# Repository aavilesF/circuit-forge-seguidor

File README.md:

# circuit-forge-seguidor

> **Rama `seguidor-caseroV2`: lo vigente está en `v2/` (ver `v2/README.md` y `CLAUDE.md`). El resto es histórico salvo excepciones documentadas en `v2/docs/ESTADO-DOCUMENTOS.md`.**

Robot seguidor de línea para **Robolympics RMX2026** (Tecnológico de Monterrey, Campus León).
Equipo **Circuit Forge**: diseño, firmware, pruebas y registro de resultados.

## Objetivo

Construir un robot autónomo, ligero y estable que recorra el circuito en el menor tiempo posible sin salirse de la línea. Prioridad del equipo: ganar; mínimo aceptable, completar la pista sin salirse. Se busca un buen equilibrio entre precisión de los sensores y velocidad.

## Competencia

| Dato | Valor |
|---|---|
| Evento | Robolympics RMX2026, categoría Seguidores de línea |
| Fecha | Sábado 21 de noviembre de 2026, 8:00 a 16:00 h |
| Sede | Tec de Monterrey, Campus León |
| Registro | Hasta el 17 de noviembre de 2026, 6:00 pm (confirmación por correo el 18 de noviembre) |
| Donación | Alimentos por $300 MXN por robot, se entregan el 21 de noviembre al registrarse |
| Reglamento | Ver [docs/requisitos.md](docs/requisitos.md) |

Las reglas pueden modificarse a más tardar el 18 de noviembre y se comunican por correo a los equipos registrados.

## Equipo

| Integrante | Rol |
|---|---|
| Alejandro Avilés Flores | Por definir |
| Alan Uzuel Vargas Zavala | Por definir |
| Daniel Navarro Robledo | Por definir |

## Estado actual

- Repositorio creado y reglamento analizado (ver `docs/requisitos.md`).
- Microcontrolador: **ESP32** (decidido, D3). El resto de la arquitectura sigue como propuesta sin aprobar (`docs/plan.md`).
- Componentes: **sin comprar** (compra prevista la semana del 2 de noviembre). El sensor (QTR-8A o curvo de 24) sigue sin decidir.
- Firmware: **lógica probada en computadora** (60 pruebas) y **simulador** de la pista. Capa de hardware del ESP32 escrita pero **solo verificada de sintaxis**: no se ha compilado con el SDK real ni probado en la placa.
- Diagramas y guía de armado listos; las medidas de las piezas son nominales hasta tenerlas en la mano.
- Pista de práctica: **por construir**.

## Contenido

| Archivo | Para qué sirve |
|---|---|
| [docs/requisitos.md](docs/requisitos.md) | Restricciones del reglamento y de la convocatoria |
| [docs/presupuesto.md](docs/presupuesto.md) | Lista de compra y presupuesto |
| [docs/decisiones.md](docs/decisiones.md) | Registro de decisiones del equipo |
| [docs/plan.md](docs/plan.md) | Plan de 4 semanas y arquitectura propuesta (aún sin aprobar) |
| [docs/contexto-ia.md](docs/contexto-ia.md) | Resumen del proyecto y prompt de arranque para que cualquier IA o persona parta del mismo contexto |
| [modificaciones/](modificaciones/README.md) | Propuestas de cambio de cada integrante, sin tocar los documentos originales |

| [docs/simulacion.md](docs/simulacion.md) | Modelo virtual, matemáticas explicadas, resultados y límites del simulador |
| [docs/electronica.md](docs/electronica.md) | Reglas eléctricas, pines (`docs/diagramas/pines.md`), batería y sensores |
| [docs/mecanica.md](docs/mecanica.md) | Geometría, velocidades, distribución de peso |
| [docs/armado.md](docs/armado.md) | Guía de armado y pruebas por etapas, con criterios de aprobado |
| `docs/diagramas/` | Diagrama de bloques, cableado, vistas superiores a escala y gráficas de simulación |
| `firmware/seguidor/` | Firmware (ESP32, Arduino IDE o PlatformIO): `pines.h` es la única fuente de los pines |
| `pruebas/` | `ejecutar.sh` (lógica, g++) y `verificar_sintaxis_esp32.sh` (hardware contra un stub) |
| `simulacion/` | Simulador en lazo cerrado que usa el mismo código de control; resultados en `resultados/` |
| `herramientas/generar_diagramas.py` | Regenera diagramas, tabla de pines y gráficas |

### Comandos rápidos

```bash
pruebas/ejecutar.sh                    # pruebas de la lógica
simulacion/ejecutar.sh                 # simulación con los parámetros por defecto
pruebas/verificar_sintaxis_esp32.sh    # sintaxis del código de hardware (no es compilación real)
python3 herramientas/generar_diagramas.py
```

## Forma de trabajo

- Cambios pequeños con commits descriptivos.
- Los cambios propuestos por los integrantes van en `modificaciones/` (ver su README), no directamente en `README.md` ni en `docs/`.
- Toda decisión de hardware o de interfaces se anota en `docs/decisiones.md`.
- Nada se da por terminado sin evidencia (foto, medición o registro de prueba).

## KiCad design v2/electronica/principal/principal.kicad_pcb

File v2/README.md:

# Seguidor de Línea V2 — rama `seguidor-caseroV2`

Creada el 12 nov 2026 desde `engineering/robot-casero` (commit f9a4700). **Todo lo vigente está en `v2/`.**
El resto de carpetas del repositorio (docs/, electronica/kicad/, mecanica/, firmware/, robot-casero/) se heredó de la rama
anterior y es **HISTÓRICO**: sirve de consulta, no es diseño vigente. No se borró nada.

| Carpeta | Contenido | Estado |
|---|---|---|
| `v2/docs/decisiones.md` | Decisiones vigentes (D-V2-xx) con su origen | vigente |
| `v2/inventario.csv` | **Fuente maestra del inventario** (comprado / usado / recepción) | vigente |
| `v2/docs/componentes.md` | Tabla **generada** desde el inventario; no se edita a mano | vigente |
| `v2/docs/ESTADO-DOCUMENTOS.md` | Qué documentos son vigentes y cuáles históricos | vigente |
| `v2/herramientas/validar_repo.py` | Validador de coherencia (inventario vs esquemas, términos obsoletos, IDs, DRC) | vigente |
| `docs/pendientes-por-confirmar.md` | **Lista única de pendientes** (v10, incluye P-V2-xx) | vigente |
| `v2/docs/conexiones.md` | Qué se conecta con qué y por qué; análisis 3.3 V vs 5 V | vigente |
| `v2/docs/bibliotecas.md` | Qué símbolo usa cada pieza y de dónde viene | vigente |
| `v2/docs/migracion.md` | Qué se migró, qué se corrigió y qué queda histórico | vigente |
| `v2/electronica/principal/` y `sensores/` | Esquemáticos KiCad 10 (copia de los de `SDL V2 General/KiCAD/Esquemas V2`) | esquemas aprobados (D-V2-20) |
| `v2/electronica/principal/` y `sensores/` `.kicad_pcb` | PCB ruteadas, DRC 0 errores (15 nov); sensores = opción B (D-V2-25); la A en `sensores/alternativa_68mm_curva/` | en revisión de Alan |
| `v2/electronica/prototipo-emergencia/` | Prototipo de emergencia en placa perforada: esquema unificado y `GUIA-FIRMWARE.md` | vigente, alternativa (D-V2-40) |
| `v2/firmware/emergencia/` | **Firmware vigente** del prototipo de emergencia, versión 2.0 (carga, consola, ajustes sin recompilar, primera conexión) | compilado y probado en PC; falta prueba física (EM-08) |
| `v2/electronica/vistas/` | SVG/PNG de esquemas y vistas 3D de la colocación | — |
| `v2/docs/evaluaciones.md` | Encoders/aprendizaje y ventilador (EN ESTUDIO) | — |
| `v2/electronica/herramientas/` | Scripts que generan esquemas, colocación y ruteo | — |

Etapas: 1 esquemáticos (aprobados) → 2 PCB de doble cara (ruteadas, en revisión; sin archivos de fabricación) → 3 compatibilidad mecánica.
Reglas de trabajo: `CLAUDE.md` en la raíz.

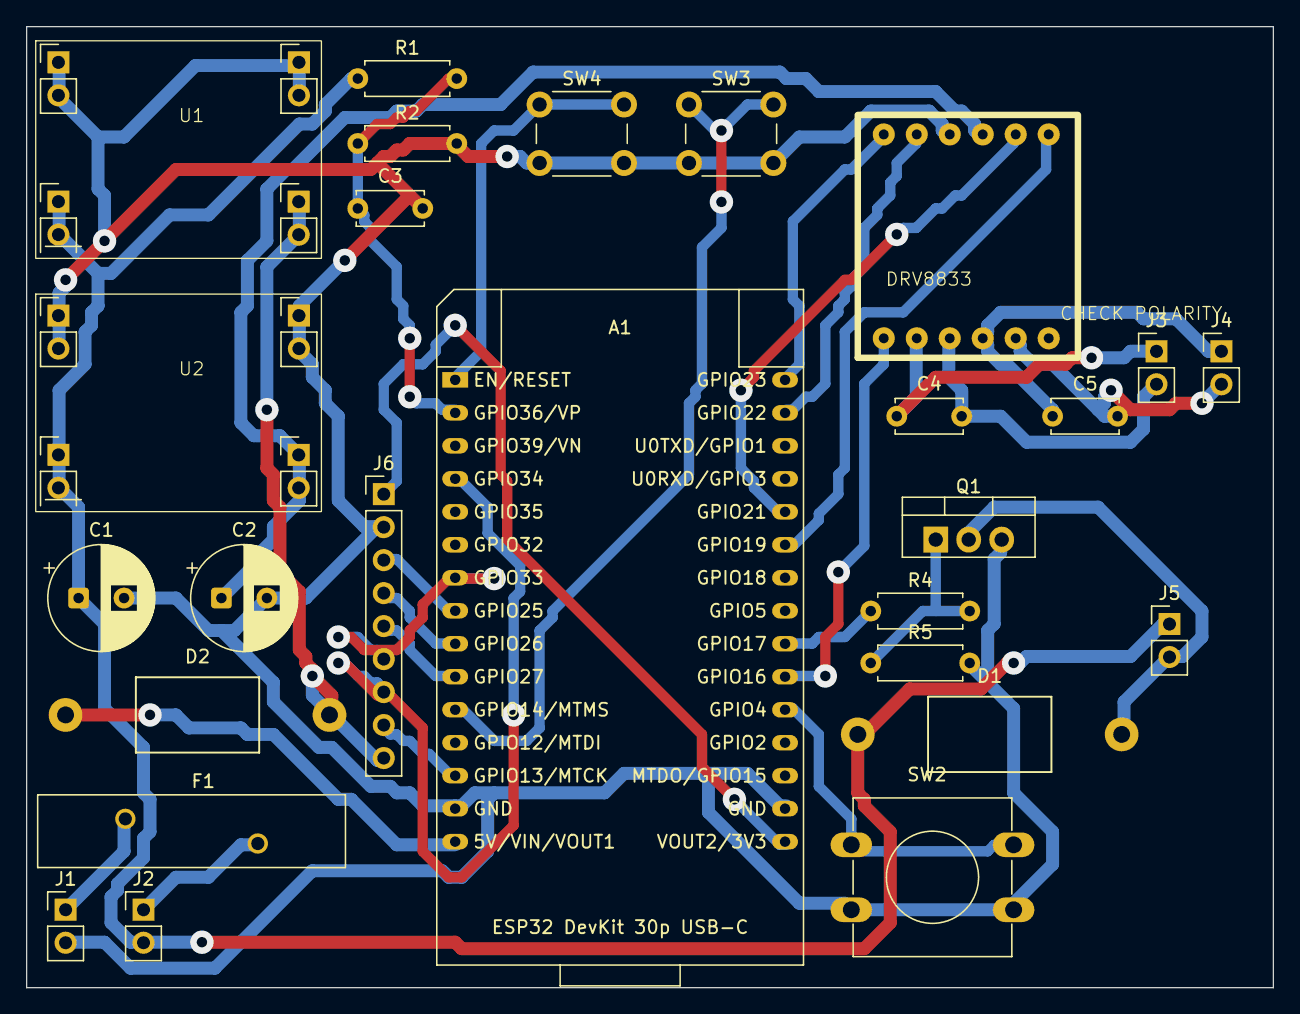
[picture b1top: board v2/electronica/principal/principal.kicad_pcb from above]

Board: 2 copper layers, 96.0 x 74.0 mm, 26 parts (0 on the bottom side), 30 nets.

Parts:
A1: ESP32 DevKit 30p USB-C; ESP32-DevKit-USB-C
C1, C2: 470uF 16V; CP_Radial_D8.0mm_P3.50mm
C3, C4, C5: 100nF; C_Disc_D5.0mm_W2.5mm_P5.00mm
D1, D2: 1N5822; D_DO-201AD_P20.32mm_Taladro1.3
F1: PTC 1.5A >=16V (por comprar); Fuse_BelFuse_0ZRE0150FF_L23.4mm_W5.3mm
J1: Bateria JST-RC; PinHeader_1x02_P2.54mm_Vertical
J2: Interruptor KCD1; PinHeader_1x02_P2.54mm_Vertical
J3: Motor izq.; PinHeader_1x02_P2.54mm_Vertical
J4: Motor der.; PinHeader_1x02_P2.54mm_Vertical
J5: Ventilador; PinHeader_1x02_P2.54mm_Vertical
J6: A sensores; PinHeader_1x09_P2.54mm_Vertical
Q1: IRLZ44N; TO-220-3_Vertical
R1: 100k; R_Axial_DIN0207_L6.3mm_D2.5mm_P7.62mm_Horizontal
R2: 33k; R_Axial_DIN0207_L6.3mm_D2.5mm_P7.62mm_Horizontal
R4: 100; R_Axial_DIN0207_L6.3mm_D2.5mm_P7.62mm_Horizontal
R5: 10k; R_Axial_DIN0207_L6.3mm_D2.5mm_P7.62mm_Horizontal
SW2: START 12x12; SW_PUSH-12mm
SW3: CAL 6x6; SW_PUSH_6mm
SW4: RESET 6x6; SW_PUSH_6mm
U1: MP1584 -> 5.0 V; MP1584module
U2: MP1584 -> 6.0 V (motores); MP1584module
U3: Modulo DRV8833; DRV8833

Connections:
+3V3: A1.16, J6.1
/+5V: D2.2, J6.9, U1.4
/+6V_MOT: C2.1, U2.4, U3.10
/AIN1: A1.25, U3.7
/AIN2: A1.26, U3.8
/BIN1: A1.29, U3.11
/BIN2: A1.30, U3.12
/CAL: A1.11, SW3.1
/DRV_SLEEP: A1.21, U3.1
/EMIT_EN: A1.13, J6.8
/EN: A1.1, SW4.1
/ESP_5V: A1.15, D2.1
/FAN_G: Q1.1, R4.2, R5.1
/FAN_PWM: A1.22, R4.1
/FAN_SW: D1.2, J5.2, Q1.2
/MOTL_A: C4.1, J3.1, U3.2
/MOTL_B: C4.2, J3.2, U3.3
/MOTR_A: C5.1, J4.1, U3.4
/MOTR_B: C5.2, J4.2, U3.5
/S0: A1.8, J6.3
/S1: A1.9, J6.4
/S2: A1.10, J6.5
/S3: A1.7, J6.6
/SIG: A1.4, J6.7
/START: A1.20, SW2.1
/VBAT_F: F1.2, J2.1
/VBAT_RAW: F1.1, J1.1
/VBAT_SENSE: A1.2, C3.1, R1.2, R2.1
/VBAT_SW: C1.1, D1.1, J2.2, J5.1, R1.1, U1.1, U2.1
GND: A1.14, A1.17, C1.2, C2.2, C3.2, J1.2, J6.2, Q1.3, R2.2, R5.2, SW2.2, SW3.2, SW4.2, U1.2, U1.3, U2.2, U2.3, U3.9

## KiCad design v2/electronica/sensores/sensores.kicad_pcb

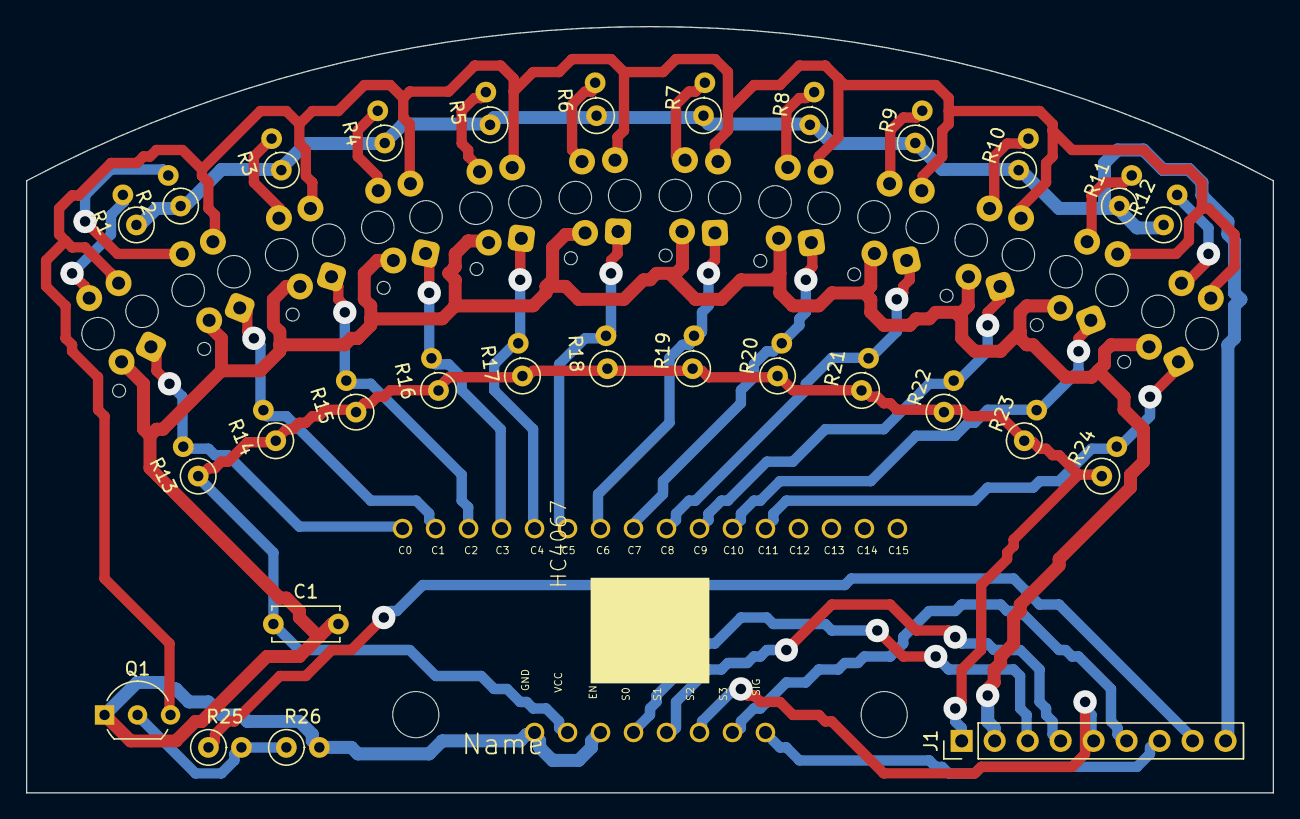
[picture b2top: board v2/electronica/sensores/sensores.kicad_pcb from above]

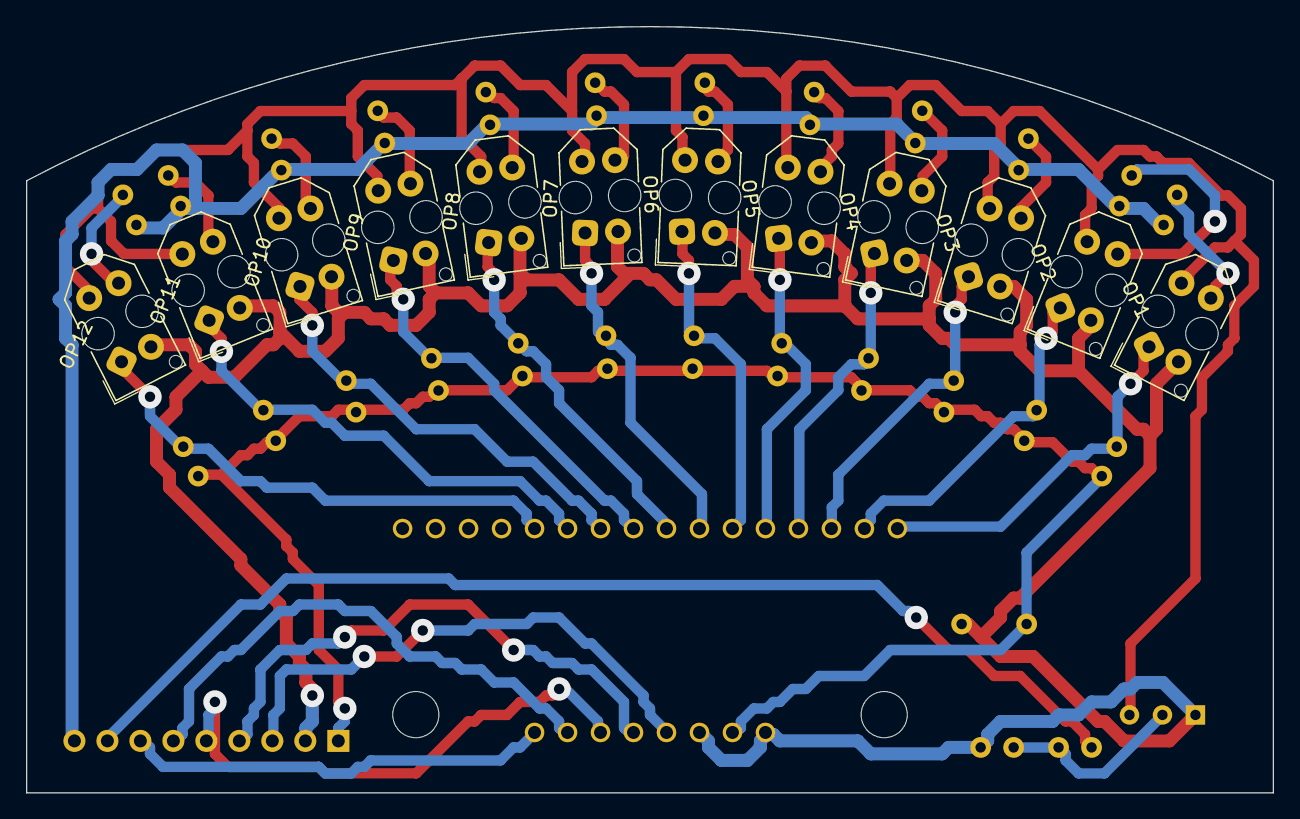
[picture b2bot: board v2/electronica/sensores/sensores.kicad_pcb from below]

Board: 2 copper layers, 96.0 x 59.0 mm, 42 parts (12 on the bottom side), 35 nets.

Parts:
C1: 100nF; C_Disc_D5.0mm_W2.5mm_P5.00mm
J1: A principal; PinHeader_1x09_P2.54mm_Vertical
OP1, OP2, OP3, OP4, OP5, OP6, OP7, OP8, OP9, OP10, OP11, OP12: TCRT5000; Vishay_TCRT5000
Q1: 2N2222 E-B-C; TO-92_Inline_Wide
R1, R2, R3, R4, R5, R6, R7, R8, R9, R10, R11, R12: 220; R_Axial_DIN0207_L6.3mm_D2.5mm_P2.54mm_Vertical
R13, R14, R15, R16, R17, R18, R19, R20, R21, R22, R23, R24, R26: 10k; R_Axial_DIN0207_L6.3mm_D2.5mm_P2.54mm_Vertical
R25: 470; R_Axial_DIN0207_L6.3mm_D2.5mm_P2.54mm_Vertical
U1: Modulo CD74HC4067; ANALOG_MUX_BREAKOUT_HC4067

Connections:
+3V3: C1.1, J1.1, R13.1, R14.1, R15.1, R16.1, R17.1, R18.1, R19.1, R20.1, R21.1, R22.1, R23.1, R24.1, U1.VCC
+5V: J1.9, R1.1, R2.1, R3.1, R4.1, R5.1, R6.1, R7.1, R8.1, R9.1, R10.1, R11.1, R12.1
/BASE_Q1: Q1.2, R25.2, R26.1
/EMIT_EN: J1.8, R25.1
/EMIT_K: OP1.4, OP2.4, OP3.4, OP4.4, OP5.4, OP6.4, OP7.4, OP8.4, OP9.4, OP10.4, OP11.4, OP12.4, Q1.3
/LEDA1: OP1.3, R1.2
/LEDA2: OP2.3, R2.2
/LEDA3: OP3.3, R3.2
/LEDA4: OP4.3, R4.2
/LEDA5: OP5.3, R5.2
/LEDA6: OP6.3, R6.2
/LEDA7: OP7.3, R7.2
/LEDA8: OP8.3, R8.2
/LEDA9: OP9.3, R9.2
/LEDA10: OP10.3, R10.2
/LEDA11: OP11.3, R11.2
/LEDA12: OP12.3, R12.2
/S0: J1.3, U1.S0
/S1: J1.4, U1.S1
/S2: J1.5, U1.S2
/S3: J1.6, U1.S3
/SEN1: OP1.1, R13.2, U1.C0
/SEN2: OP2.1, R14.2, U1.C1
/SEN3: OP3.1, R15.2, U1.C2
/SEN4: OP4.1, R16.2, U1.C3
/SEN5: OP5.1, R17.2, U1.C4
/SEN6: OP6.1, R18.2, U1.C5
/SEN7: OP7.1, R19.2, U1.C6
/SEN8: OP8.1, R20.2, U1.C7
/SEN9: OP9.1, R21.2, U1.C8
/SEN10: OP10.1, R22.2, U1.C9
/SEN11: OP11.1, R23.2, U1.C10
/SEN12: OP12.1, R24.2, U1.C11
/SIG: J1.7, U1.SIG
GND: C1.2, J1.2, OP1.2, OP2.2, OP3.2, OP4.2, OP5.2, OP6.2, OP7.2, OP8.2, OP9.2, OP10.2, OP11.2, OP12.2, Q1.1, R26.2, U1.EN, U1.GND

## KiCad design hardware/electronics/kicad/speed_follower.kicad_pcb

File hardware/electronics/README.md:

# Electrónica — PCB-chasis (KiCad 9)

La placa es el chasis del robot: 4 capas, 130 × 92 mm, con los 16 sensores en la cara inferior. Todo el diseño eléctrico
se **genera** desde una sola fuente (`generador/diseno.py`), así que el esquemático, la PCB, la BOM y los pines del
firmware no pueden divergir.

```
generador/diseno.py ──► esquematico.py ──► kicad/*.kicad_sch ──► netlist (kicad-cli)
        │                                                              │
        ├──► pcb_plan.py ──► plan_pcb.json ◄─────── nombres de red ────┘
        │         │
        │         ├──► pcb_kicad.py construir ──► colocar.py (legaliza cortijos) ──► enrutar.py ──► rutas.json
        │         └──► pcb_kicad.py final + rellenar_zonas.py ──► kicad/speed_follower.kicad_pcb
        ├──► herramientas/generar_bom.py ──► docs/BOM_FINAL.csv, fabricacion/bom_ensamblaje.csv
        └──► herramientas/generar_config_firmware.py ──► firmware/stm32/src/pines_generados.h
```

## Contenido

| Ruta | Qué es |
|---|---|
| `kicad/` | **Proyecto KiCad 9 editable**: `speed_follower.kicad_pro`, esquemático jerárquico (raíz + 5 hojas: alimentación, MCU, motores, sensores, mecánica), `speed_follower.kicad_pcb` ruteada con planos, biblioteca propia `circuitforge.kicad_sym` (QRE1113GR), `sym-lib-table`, `fp-lib-table`, `3d/` (2 modelos aproximados) |
| `generador/` | Scripts que generan todo lo anterior (`diseno.py` partes y redes, `esquematico.py`, `pcb_plan.py`, `pcb_kicad.py`, `colocar.py`, `enrutar.py`, `rellenar_zonas.py`, `modelos3d.py`) y sus datos intermedios |
| `herramientas/` | `kicad.sh` (kicad-cli), `verificar_conectividad.py` (diseño = esquemático = PCB), `resumen_verificacion.py` (filtro de ERC/DRC), `verificar_modelos3d.py`, `calculos_electricos.py`, `ver_colocacion.py` |
| `verificacion/` | Reportes de ERC y DRC (`.rpt` y `.json`), `RESUMEN.md`, `modelos3d.md`, netlist del esquemático, pads de la PCB |
| `fabricacion/` | Paquete para el fabricante: Gerbers, taladros, contorno DXF, pick and place, BOM de ensamblaje, planos de ensamblaje, PDF, STEP. Ver [`fabricacion/LEEME.md`](fabricacion/LEEME.md) |
| `pcba/` | Vistas de la PCBA: 2D superior e inferior (SVG con referencias y cotas) y 3D superior, inferior e isométrica (PNG de 3200 × 2400) |

## Reglas de diseño

Separación 0.15 mm; pistas 0.2 mm (señal), 0.4 mm (+3V3 y lógica del puente H), 0.5 mm (motores), 0.8 mm (batería);
vías 0.55/0.25 mm; cobre al borde 0.3 mm. In1.Cu = GND y In2.Cu = +3V3 completos; rellenos de GND en ambas caras.
El bus PWM del MCU al DRV8833 se traza a mano (4 pistas paralelas, `enrutar.py`, `BUS_PWM`); el resto lo rutea
`enrutar.py` (A* en rejilla de 0.05 mm con separación exacta, árbol de expansión mínima y reparación por arranque).
Corrientes, caídas, disipación y tiempos: [`docs/CALCULOS_ELECTRICOS.md`](../../docs/CALCULOS_ELECTRICOS.md).

## Regenerar y verificar

```bash
hardware/electronics/generar_fabricacion.sh            # esquemático -> PCB -> ERC/DRC/paridad -> conectividad -> paquete
hardware/electronics/generar_fabricacion.sh --enrutar  # además vuelve a colocar y rutear (≈ 10-20 min)
```

El script se detiene **antes** de escribir Gerbers si el ERC o el DRC tienen errores, o avisos que no estén en la lista de
excepciones justificadas de `herramientas/resumen_verificacion.py` (hoy: 2 avisos del ERC por AISEN/BISEN del DRV8833 a
GND, que la hoja de datos indica cuando no se usa la regulación de corriente).

Requisitos: KiCad 9 (`kicad-cli` y el módulo `pcbnew` de su Python) y Python 3 con numpy, numba, scipy, shapely y
matplotlib. En Windows, abrir `kicad/speed_follower.kicad_pro` con KiCad 9 basta para revisar o editar; para regenerar,
usar el "KiCad 9.0 Command Prompt" con `PY_KICAD=python` y Git Bash para el script.

## Estado

ERC, DRC con paridad, conectividad y modelos 3D verificados (`verificacion/RESUMEN.md`, `verificacion/modelos3d.md`).
**Validación EDA, no física**: la placa no se ha fabricado.

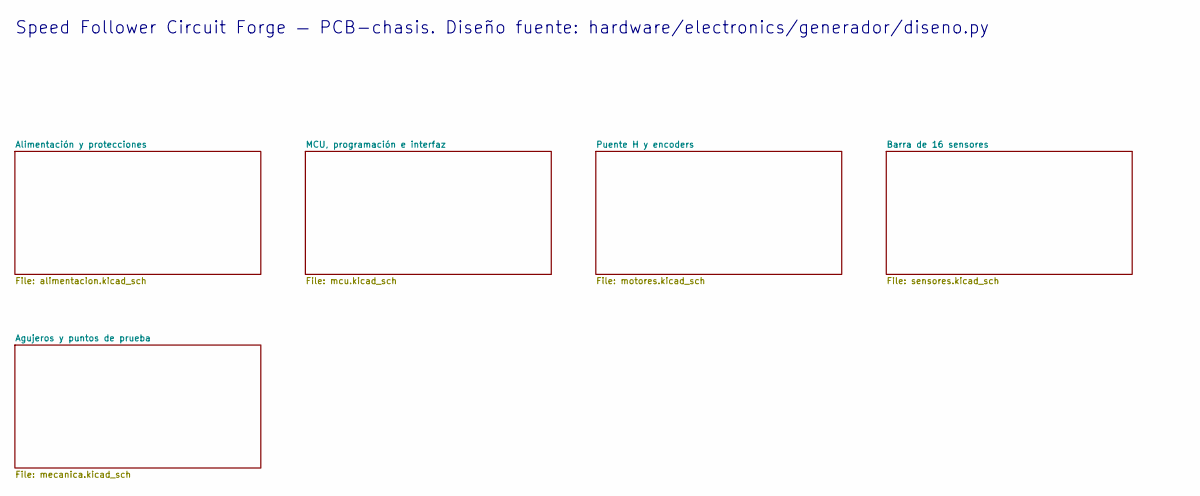
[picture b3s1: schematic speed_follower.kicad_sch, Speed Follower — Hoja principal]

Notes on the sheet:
Speed Follower Circuit Forge — PCB-chasis. Diseño fuente: hardware/electronics/generador/diseno.py

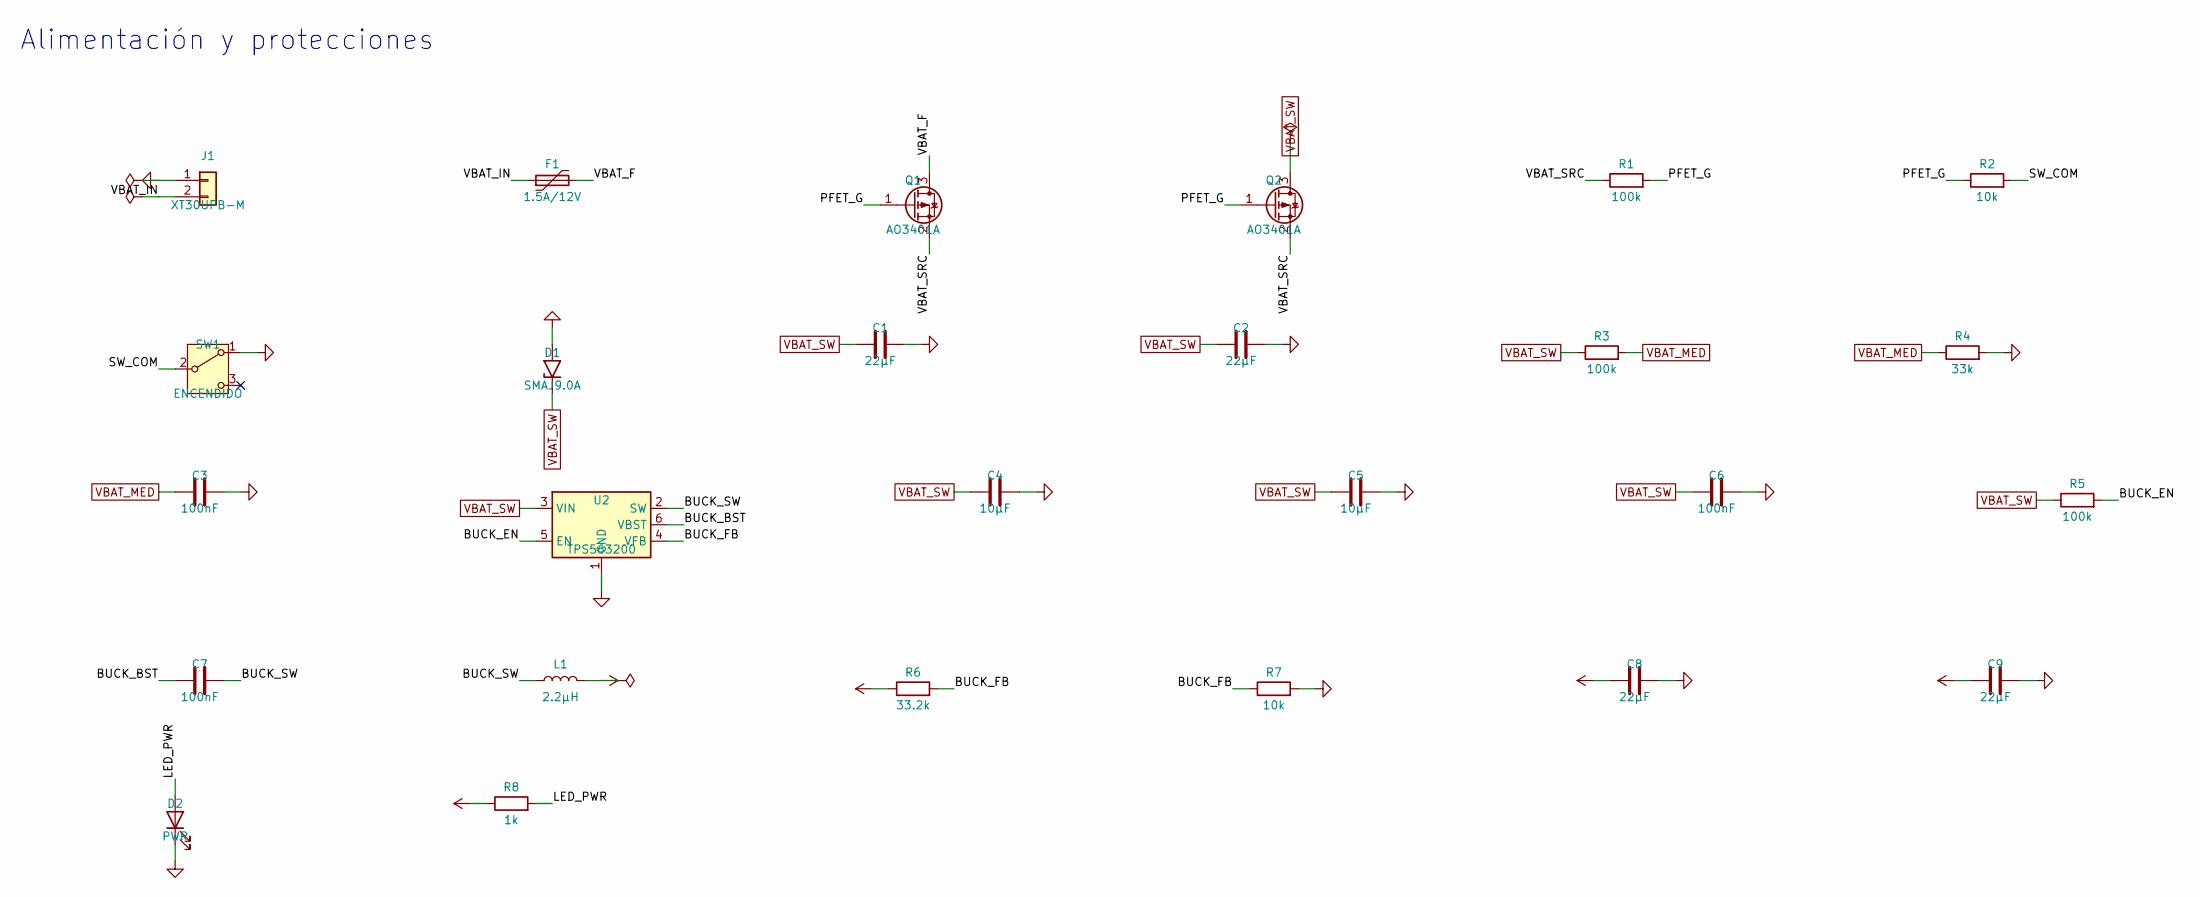
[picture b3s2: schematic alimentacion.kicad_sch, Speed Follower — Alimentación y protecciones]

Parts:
C1, C2, C8, C9: 22µF; C_0805_2012Metric; MPN GRM21BR61E226ME44L
C3, C6, C7: 100nF; C_0402_1005Metric; MPN GRM155R71C104KA88D
C4, C5: 10µF; C_0805_2012Metric; MPN GRM21BR61E106KA73L
D1: SMAJ9.0A; D_SMA; MPN SMAJ9.0A
D2: PWR; LED_0603_1608Metric; MPN APT1608SGC
F1: 1.5A/12V; Fuse_1812_4532Metric; MPN 1812L150/12DR
J1: XT30UPB-M; AMASS_XT30UPB-M_1x02_P5.0mm_Vertical; MPN XT30UPB-M
L1: 2.2µH; L_Wuerth_MAPI-4030; MPN 74438357022
Q1, Q2: AO3401A; SOT-23; MPN AO3401A
R1, R3, R5: 100k; R_0402_1005Metric; MPN RC0402FR-07100KL
R2, R7: 10k; R_0402_1005Metric; MPN RC0402FR-0710KL
R4: 33k; R_0402_1005Metric; MPN RC0402FR-0733KL
R6: 33.2k; R_0402_1005Metric; MPN RC0402FR-0733K2L
R8: 1k; R_0402_1005Metric; MPN RC0402FR-071KL
SW1: ENCENDIDO; SW_Slide_SPDT_Angled_CK_OS102011MA1Q; MPN OS102011MA1QN1
U2: TPS563200; SOT-23-6; MPN TPS563200DDCR

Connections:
+3V3: C8.1, C9.1, L1.2, R6.1, R8.1; also elsewhere on the board
/Alimentación y protecciones/BUCK_BST: C7.1, U2.6 (VBST)
/Alimentación y protecciones/BUCK_EN: R5.2, U2.5 (EN)
/Alimentación y protecciones/BUCK_FB: R6.2, R7.1, U2.4 (VFB)
/Alimentación y protecciones/BUCK_SW: C7.2, L1.1, U2.2 (SW)
/Alimentación y protecciones/LED_PWR: D2.2 (A), R8.2
/Alimentación y protecciones/PFET_G: Q1.1 (G), Q2.1 (G), R1.2, R2.1
/Alimentación y protecciones/SW_COM: R2.2, SW1.2 (B)
/Alimentación y protecciones/VBAT_F: F1.2, Q1.3 (D)
/Alimentación y protecciones/VBAT_IN: F1.1, J1.2
/Alimentación y protecciones/VBAT_SRC: Q1.2 (S), Q2.2 (S), R1.1
GND: C1.2, C2.2, C3.2, C4.2, C5.2, C6.2, C8.2, C9.2, D1.2 (A2), D2.1 (K), J1.1, R4.2, R7.2, SW1.1 (A), U2.1 (GND); also elsewhere on the board
VBAT_MED: C3.1, R3.2, R4.1; also elsewhere on the board
VBAT_SW: C1.1, C2.1, C4.1, C5.1, C6.1, D1.1 (A1), Q2.3 (D), R3.1, R5.1, U2.3 (VIN); also elsewhere on the board

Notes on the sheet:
Alimentación y protecciones

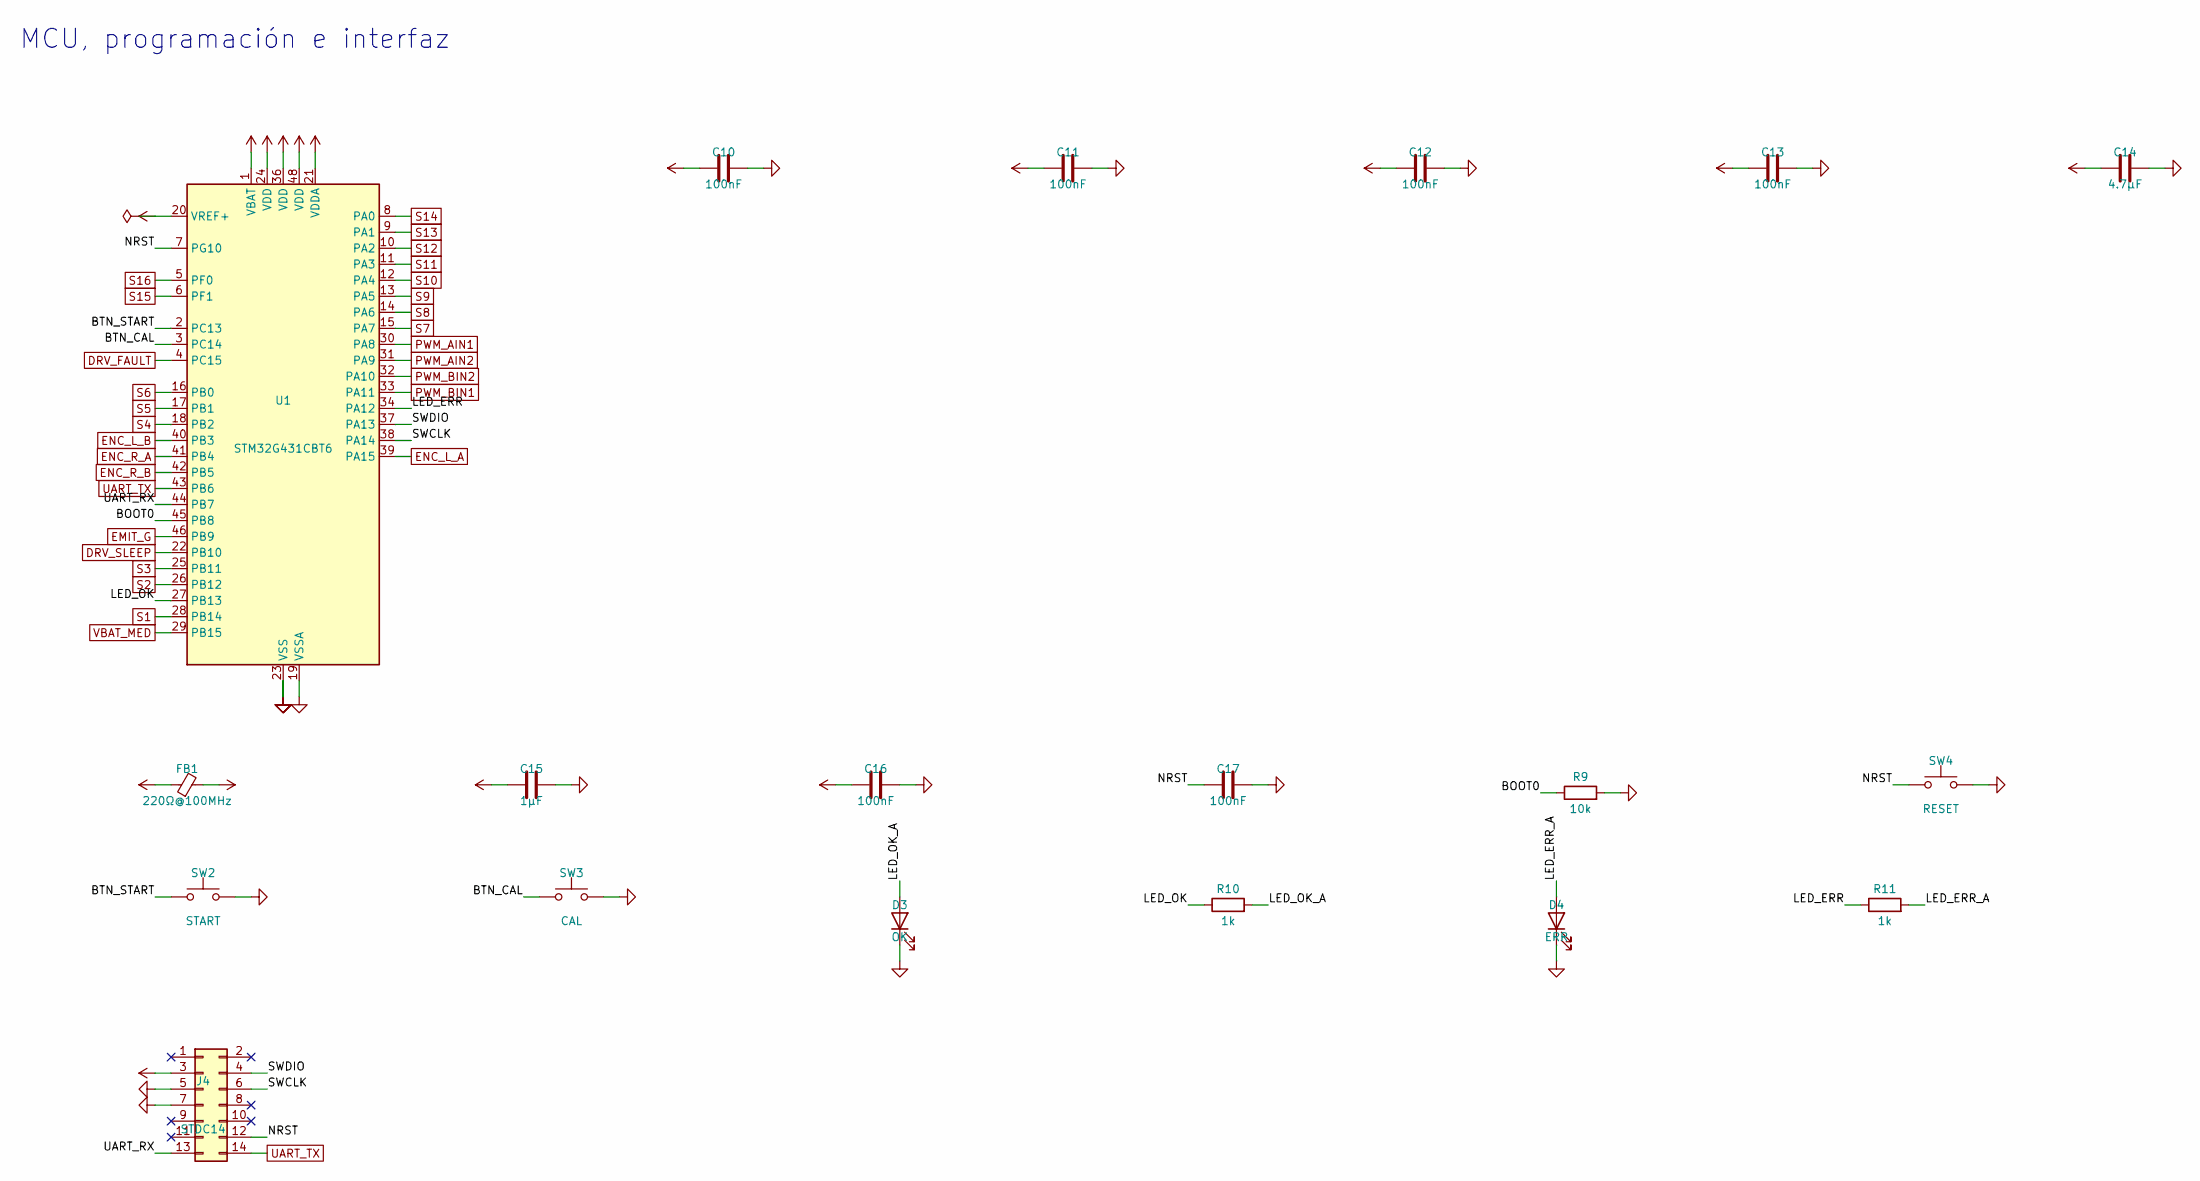
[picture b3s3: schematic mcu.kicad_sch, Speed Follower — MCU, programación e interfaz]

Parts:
C10, C11, C12, C13, C16, C17: 100nF; C_0402_1005Metric; MPN GRM155R71C104KA88D
C14: 4.7µF; C_0603_1608Metric; MPN GRM188R61A475KE15D
C15: 1µF; C_0402_1005Metric; MPN GRM155R61A105KE15D
D3: OK; LED_0603_1608Metric; MPN APT1608SGC
D4: ERR; LED_0603_1608Metric; MPN APT1608EC
FB1: 220Ω@100MHz; L_0603_1608Metric; MPN BLM18PG221SN1D
J4: STDC14; PinHeader_2x07_P1.27mm_Vertical; MPN M50-3500742
R9: 10k; R_0402_1005Metric; MPN RC0402FR-0710KL
R10, R11: 1k; R_0402_1005Metric; MPN RC0402FR-071KL
SW2: START; SW_SPST_Omron_B3FS-100xP; MPN B3FS-1000P
SW3: CAL; SW_SPST_Omron_B3FS-100xP; MPN B3FS-1000P
SW4: RESET; SW_SPST_B3U-1000P; MPN B3U-1000P
U1: STM32G431CBT6; LQFP-48_7x7mm_P0.5mm; MPN STM32G431CBT6

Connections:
+3V3: C10.1, C11.1, C12.1, C13.1, C14.1, FB1.1, J4.3, U1.1 (VBAT), U1.24 (VDD), U1.36 (VDD), U1.48 (VDD); also elsewhere on the board
+3V3A: C15.1, C16.1, FB1.2, U1.20 (VREF+), U1.21 (VDDA); also elsewhere on the board
/MCU, programación e interfaz/BOOT0: R9.1, U1.45 (PB8)
/MCU, programación e interfaz/BTN_CAL: SW3.1, U1.3 (PC14)
/MCU, programación e interfaz/BTN_START: SW2.1, U1.2 (PC13)
/MCU, programación e interfaz/LED_ERR: R11.1, U1.34 (PA12)
/MCU, programación e interfaz/LED_ERR_A: D4.2 (A), R11.2
/MCU, programación e interfaz/LED_OK: R10.1, U1.27 (PB13)
/MCU, programación e interfaz/LED_OK_A: D3.2 (A), R10.2
/MCU, programación e interfaz/NRST: C17.1, J4.12, SW4.1, U1.7 (PG10)
/MCU, programación e interfaz/SWCLK: J4.6, U1.38 (PA14)
/MCU, programación e interfaz/SWDIO: J4.4, U1.37 (PA13)
/MCU, programación e interfaz/UART_RX: J4.13, U1.44 (PB7)
DRV_FAULT: U1.4 (PC15); also elsewhere on the board
DRV_SLEEP: U1.22 (PB10); also elsewhere on the board
EMIT_G: U1.46 (PB9); also elsewhere on the board
ENC_L_A: U1.39 (PA15); also elsewhere on the board
ENC_L_B: U1.40 (PB3); also elsewhere on the board
ENC_R_A: U1.41 (PB4); also elsewhere on the board
ENC_R_B: U1.42 (PB5); also elsewhere on the board
GND: C10.2, C11.2, C12.2, C13.2, C14.2, C15.2, C16.2, C17.2, D3.1 (K), D4.1 (K), J4.5, J4.7, R9.2, SW2.2, SW3.2, SW4.2, U1.19 (VSSA), U1.23 (VSS), U1.35 (VSS), U1.47 (VSS); also elsewhere on the board
PWM_AIN1: U1.30 (PA8); also elsewhere on the board
PWM_AIN2: U1.31 (PA9); also elsewhere on the board
PWM_BIN1: U1.33 (PA11); also elsewhere on the board
PWM_BIN2: U1.32 (PA10); also elsewhere on the board
S1: U1.28 (PB14); also elsewhere on the board
S2: U1.26 (PB12); also elsewhere on the board
S3: U1.25 (PB11); also elsewhere on the board
S4: U1.18 (PB2); also elsewhere on the board
S5: U1.17 (PB1); also elsewhere on the board
S6: U1.16 (PB0); also elsewhere on the board
S7: U1.15 (PA7); also elsewhere on the board
S8: U1.14 (PA6); also elsewhere on the board
S9: U1.13 (PA5); also elsewhere on the board
S10: U1.12 (PA4); also elsewhere on the board
S11: U1.11 (PA3); also elsewhere on the board
S12: U1.10 (PA2); also elsewhere on the board
S13: U1.9 (PA1); also elsewhere on the board
S14: U1.8 (PA0); also elsewhere on the board
S15: U1.6 (PF1); also elsewhere on the board
S16: U1.5 (PF0); also elsewhere on the board
UART_TX: J4.14, U1.43 (PB6); also elsewhere on the board
VBAT_MED: U1.29 (PB15); also elsewhere on the board

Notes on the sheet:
MCU, programación e interfaz

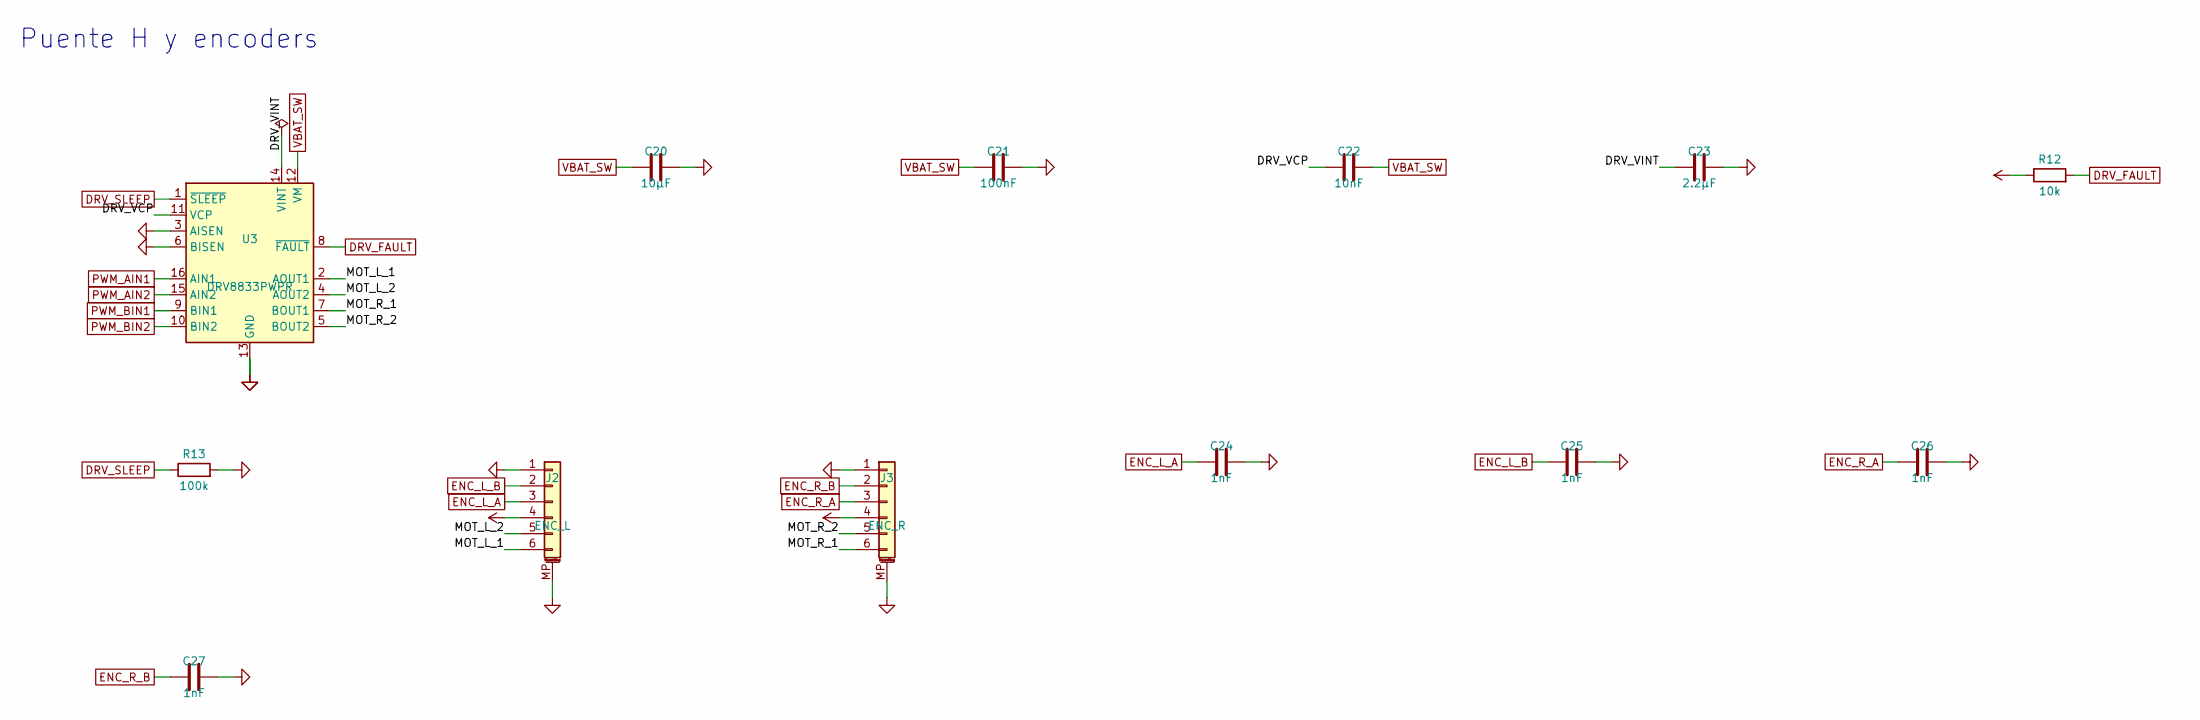
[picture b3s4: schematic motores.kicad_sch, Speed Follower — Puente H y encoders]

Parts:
C20: 10µF; C_0805_2012Metric; MPN GRM21BR61E106KA73L
C21: 100nF; C_0402_1005Metric; MPN GRM155R71C104KA88D
C22: 10nF; C_0402_1005Metric; MPN GRM155R71H103KA88D
C23: 2.2µF; C_0402_1005Metric; MPN GRM155R60J225ME15D
C24, C25, C26, C27: 1nF; C_0402_1005Metric; MPN GRM155R71H102KA01D
J2: ENC_L; JST_SH_BM06B-SRSS-TB_1x06-1MP_P1.00mm_Vertical; MPN BM06B-SRSS-TB
J3: ENC_R; JST_SH_BM06B-SRSS-TB_1x06-1MP_P1.00mm_Vertical; MPN BM06B-SRSS-TB
R12: 10k; R_0402_1005Metric; MPN RC0402FR-0710KL
R13: 100k; R_0402_1005Metric; MPN RC0402FR-07100KL
U3: DRV8833PWPR; HTSSOP-16-1EP_4.4x5mm_P0.65mm_EP3.4x5mm_Mask2.46x2.31mm_The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; MPN DRV8833PWPR

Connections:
+3V3: J2.4, J3.4, R12.1; also elsewhere on the board
/Puente H y encoders/DRV_VCP: C22.1, U3.11 (VCP)
/Puente H y encoders/DRV_VINT: C23.1, U3.14 (VINT)
/Puente H y encoders/MOT_L_1: J2.6, U3.2 (AOUT1)
/Puente H y encoders/MOT_L_2: J2.5, U3.4 (AOUT2)
/Puente H y encoders/MOT_R_1: J3.6, U3.7 (BOUT1)
/Puente H y encoders/MOT_R_2: J3.5, U3.5 (BOUT2)
DRV_FAULT: R12.2, U3.8 (~FAULT); also elsewhere on the board
DRV_SLEEP: R13.1, U3.1 (~SLEEP); also elsewhere on the board
ENC_L_A: C24.1, J2.3; also elsewhere on the board
ENC_L_B: C25.1, J2.2; also elsewhere on the board
ENC_R_A: C26.1, J3.3; also elsewhere on the board
ENC_R_B: C27.1, J3.2; also elsewhere on the board
GND: C20.2, C21.2, C23.2, C24.2, C25.2, C26.2, C27.2, J2.1, J2.MP (MountPin), J3.1, J3.MP (MountPin), R13.2, U3.3 (AISEN), U3.6 (BISEN), U3.13 (GND), U3.17 (GND); also elsewhere on the board
PWM_AIN1: U3.16 (AIN1); also elsewhere on the board
PWM_AIN2: U3.15 (AIN2); also elsewhere on the board
PWM_BIN1: U3.9 (BIN1); also elsewhere on the board
PWM_BIN2: U3.10 (BIN2); also elsewhere on the board
VBAT_SW: C20.1, C21.1, C22.2, U3.12 (VM); also elsewhere on the board

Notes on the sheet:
Puente H y encoders
